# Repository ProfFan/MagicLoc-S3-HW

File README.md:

# MagicLoc ESP32-S3 Node Hardware

# LICENSE

CERN OHL-W v2, See `LICENSE`

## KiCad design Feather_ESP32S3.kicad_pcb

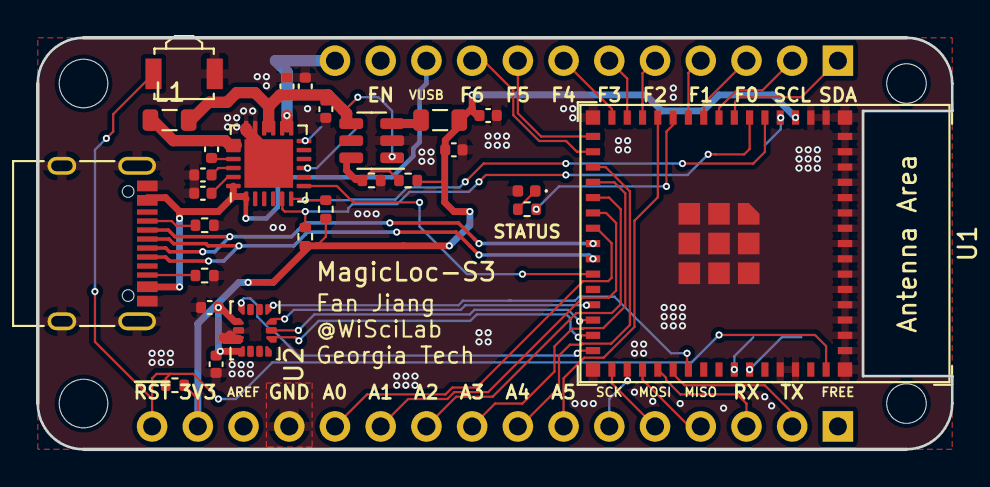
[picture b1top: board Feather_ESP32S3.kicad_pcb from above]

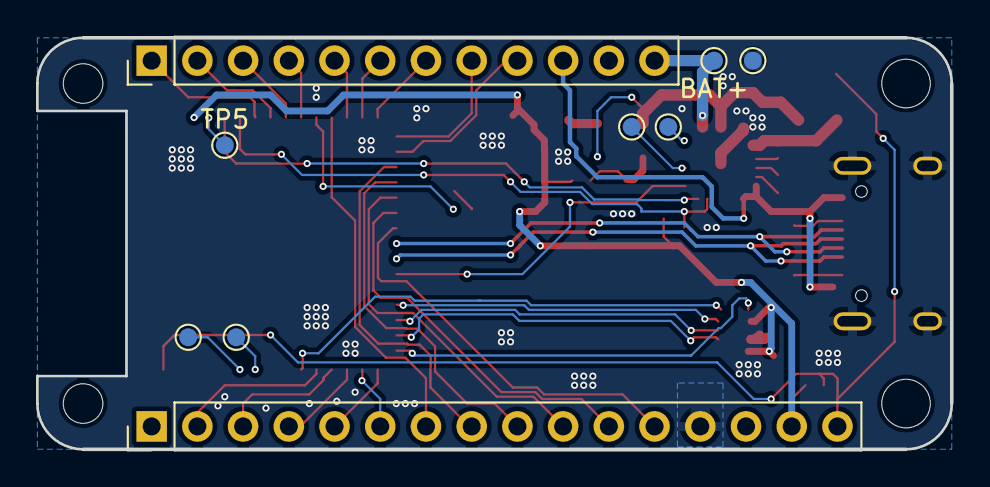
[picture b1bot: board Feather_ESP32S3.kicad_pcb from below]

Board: 2 copper layers, 50.8 x 22.9 mm, 36 parts (9 on the bottom side), 51 nets.

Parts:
C1, C6, C7: 10uF; C_0402_1005Metric
C2: 10uF 10V; C_0402_1005Metric
C3, C8, C9: 100nF; C_0402_1005Metric
C4: 47nF; C_0402_1005Metric
C5: 4.7uF; C_0402_1005Metric
C10: 4.7uF 10V; C_0402_1005Metric
D1: LED; LED_0402_1005Metric
J1: U262-16XN-4BVC11; USB_C_Receptacle_XKB_U262-16XN-4BVC11
J1#2: feather long; PinHeader_1x16_P2.54mm_Vertical
J2: feather short; PinHeader_1x12_P2.54mm_Vertical
L1: 1uH 800mA; L_0805_2012Metric
L2: 2.2uH 800mA 25mOhm; L_0805_2012Metric
R1, R2: 5.1k; R_0402_1005Metric
R3, R4, R7: 10k; R_0402_1005Metric
R5: 450k 1%; R_0402_1005Metric
R6: 100k 1%; R_0402_1005Metric
R8: 750; R_0402_1005Metric
SW1: SW_Push; SW_SPST_B3U-3000P
TP1, TP2, TP4, TP5, TP6, TP7: TestPoint; TestPoint_Pad_D1.0mm
TP3: BAT+; TestPoint_Pad_D1.0mm
U1: ESP32-S3-MINI-1
U2: LSM6DSOTR; LGA-14_3x2.5mm_P0.5mm_LayoutBorder3x4y_JLC
U3: TLV62569DDC; SOT-23-6
U4: SGM41511; QFN-24-1EP_4x4mm_P0.5mm_EP2.7x2.7mm

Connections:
+3V3: C2.1, C3.1, C8.2, C9.2, J1#2.15, L2.2, R3.1, R4.1, R5.1, R7.1, U1.3 (3V3), U2.5 (VDDIO), U2.8 (VDD)
/A0: J1#2.12, U1.22 (GPIO18/U1RXD/ADC2_CH7/CLK_OUT3)
/A1: J1#2.11, U1.21 (GPIO17/U1TXD/ADC2_CH6)
/A2: J1#2.10, U1.20 (GPIO16/U0CTS/ADC2_CH5/XTAL_32K_NH5)
/A3: J1#2.9, U1.19 (GPIO15/U0RTS/ADC2_CH4/XTAL_32K_P)
/A4: J1#2.8, U1.18 (GPIO14/TOUCH14/ADC2_CH3/FSPIWP/FSPIDQS/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)
/A5: J1#2.7, U1.12 (GPIO8/TOUCH8/ADC1_CH7/SUBSPICS1)
/BMS/~QON: TP2.1, U4.12 (~QON)
/ESP_BOOT0: TP5.1, U1.4 (GPIO0/BOOT)
/ESP_U0_RXD: TP7.1, U1.40 (U0RXD/GPIO44/CLK_OUT2)
/ESP_U0_TXD: TP6.1, U1.39 (U0TXD/GPIO43/CLK_OUT1)
/ESP_USB_DN: J1.A7 (D-), J1.B7 (D-), U1.23 (GPIO19/U1RTS/ADC2_CH8/CLK_OUT2/USB_D-)
/ESP_USB_DP: J1.A6 (D+), J1.B6 (D+), U1.24 (GPIO20/U1CTS/ADC2_CH9/CLK_OUT1/USB_D+)
/F0: J2.3, U1.9 (GPIO5/TOUCH5/ADC1_CH4)
/F1: J2.4, U1.10 (GPIO6/TOUCH6/ADC1_CH5)
/F2: J2.5, U1.13 (GPIO9/TOUCH9/ADC1_CH8/FSPIHD/SUBSPIHD)
/F3: J2.6, U1.14 (GPIO10/TOUCH10/ADC1_CH9/FSPICS0/FSPIIO4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)
/F4: J2.7, U1.15 (GPIO11/TOUCH11/ADC2_CH0/FSPID/FSPIIO5/S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)
/F5: J2.8, U1.16 (GPIO12/TOUCH12/ADC2_CH1/FSPICLK/FSPIIO6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)
/F6: J2.9, U1.17 (GPIO13/TOUCH13/ADC2_CH2/FSPIQ/FSPIIO7/S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)
/IMU_CS: U1.29 (SPIIO5/GPIO34/FSPICS0/SUBSPICS0), U2.12 (CS)
/IMU_INT1: U1.30 (GPIO48/SPICLK_N/SUBSPICLK_N_DIFF), U2.4 (INT1)
/IMU_MISO: U1.36 (MTDO/GPIO40/CLK_OUT2), U2.1 (SDO/SA0)
/IMU_MOSI: U1.27 (GPIO47/SPICLK_P/SUBSPICLK_P_DIFF), U2.14 (SDA)
/IMU_SCLK: U1.28 (SPIIO4/GPIO33/FSPIHD/SUBSPIHD), U2.13 (SCL)
/MISO: J1#2.4, U1.33 (SPIDQS/GPIO37/FSPIQ/SUBSPIQ)
/MOSI: J1#2.5, U1.31 (SPIIO6/GPIO35/FSPID/SUBSPID)
/RX: J1#2.3, U1.34 (GPIO38/FSPIWP/SUBSPIWP)
/SCK: J1#2.6, U1.32 (SPIIO7/GPIO36/FSPICLK/SUBSPICLK)
/SCL: J2.2, U1.8 (GPIO4/TOUCH4/ADC1_CH3)
/SCL_BMS: R4.2, U1.6 (GPIO2/TOUCH2/ADC1_CH1), U4.5 (SCL)
/SDA: J2.1, U1.7 (GPIO3/TOUCH3/ADC1_CH2)
/SDA_BMS: R3.2, U1.5 (GPIO1/TOUCH1/ADC1_CH0), U4.6 (SDA)
/STATUS_LED: R8.1, U1.11 (GPIO7/TOUCH7/ADC1_CH6)
/TX: J1#2.2, U1.35 (MTCK/GPIO39/CLK_OUT3/SUBSPICS1)
/VBAT: J2.12, TP3.1, U4.13 (BAT), U4.14 (BAT)
/~CE_BMS: TP1.1, U4.9 (~CE)
/~INT_BMS: U1.25 (GPIO21), U4.7 (~INT)
/~RST: J1#2.16, R7.2, SW1.1, U1.45 (EN)
GND: C1.1, C2.2, C3.2, C5.2, C6.2, C7.2, C8.1, C9.1, C10.2, D1.2 (A), J1.A1 (GND), J1.A12 (GND), J1.B1 (GND), J1.B12 (GND), J1.S1 (SHIELD), J1#2.13, R1.2, R2.2, R6.2, SW1.2, TP4.1, U1.1 (GND), U1.2 (GND), U1.42 (GND), U1.43 (GND), U1.46 (GND), U2.6 (GND), U2.7 (GND), U3.2 (GND), U4.17 (GND), U4.18 (GND), U4.25 (GND)
unnamed: C4.1, L1.1, U4.19 (SW), U4.20 (SW)
unnamed: D1.1 (K), R8.2
unnamed: J1.A5 (CC1), R1.1
unnamed: J1.B5 (CC2), R2.1
unnamed: R5.2, R6.1, U3.6 (FB)
unnamed: L2.1, U3.3 (SW)
unnamed: C4.2, U4.21 (BTST)
unnamed: C1.2, U4.23 (PMID)
unnamed: C5.1, U4.22 (REGN)
VBUS: J1.A4 (VBUS), J1.A9 (VBUS), J1.B4 (VBUS), J1.B9 (VBUS), J2.10, U4.1 (VAC), U4.24 (VBUS)
VCC: C6.1, C7.1, C10.1, L1.2, U3.1 (EN), U3.4 (VIN), U4.15 (SYS), U4.16 (SYS)

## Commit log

2022-12-27 Init
2024-01-23 Latest HW
2024-01-23 Add LICENSE
